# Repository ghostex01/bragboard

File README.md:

# bragboard
 Repository for my first custom (split) keyboard

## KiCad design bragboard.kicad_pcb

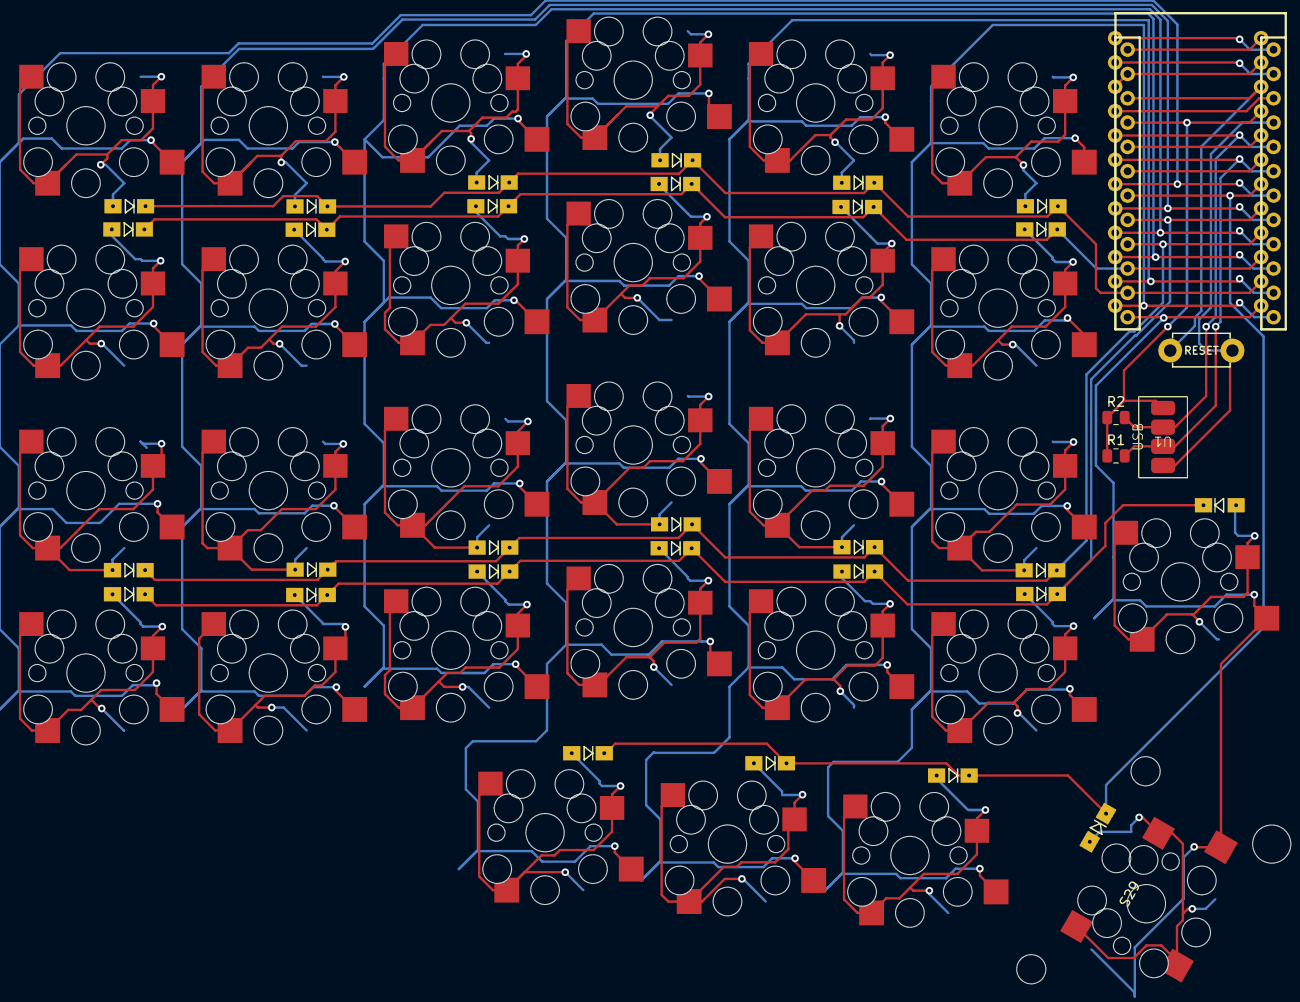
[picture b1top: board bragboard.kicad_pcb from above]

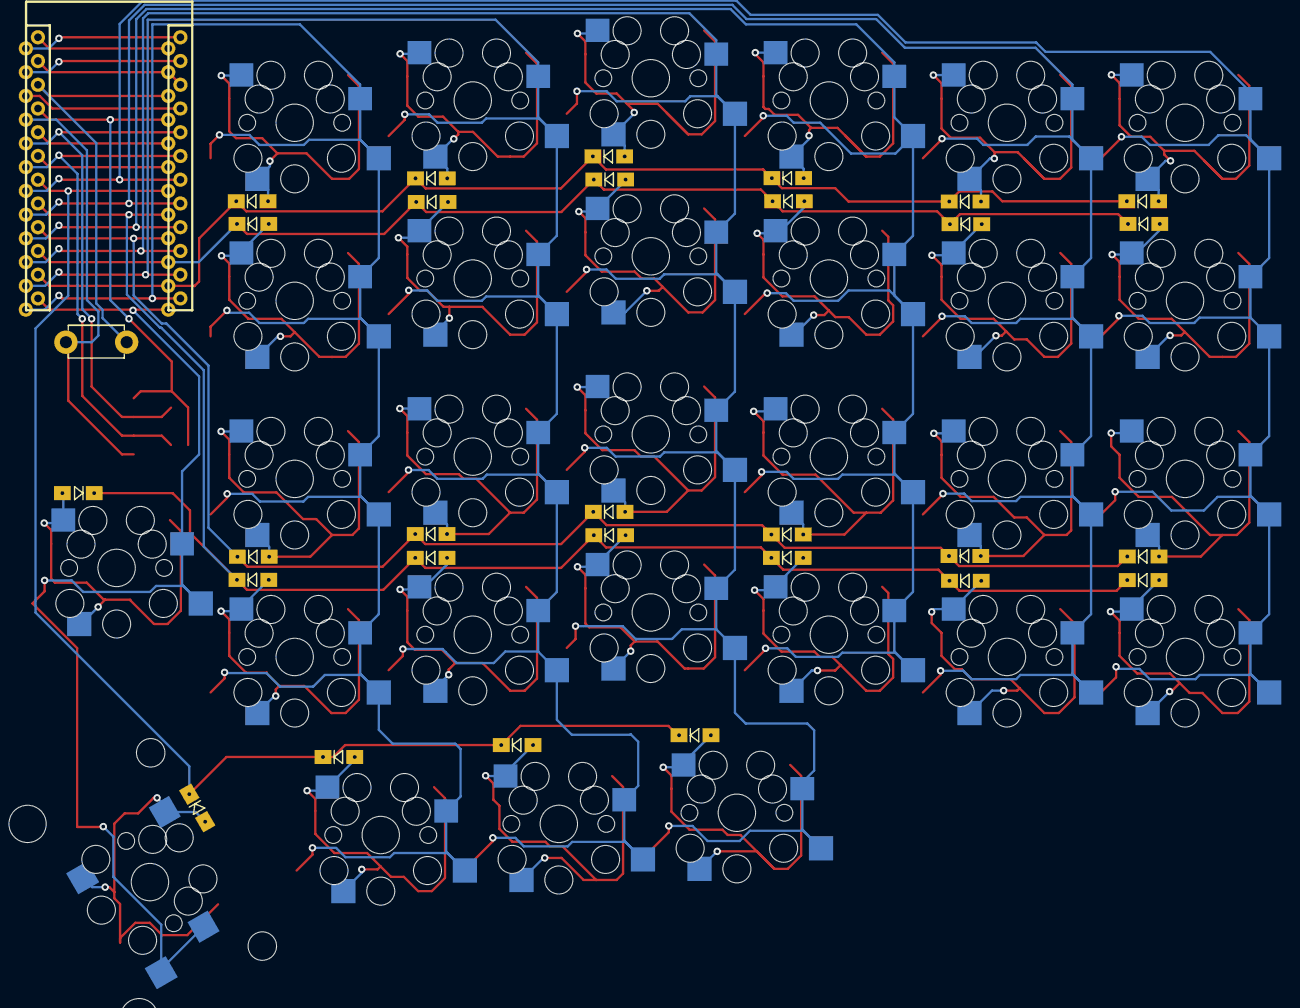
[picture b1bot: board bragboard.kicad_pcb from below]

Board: 2 copper layers, 64 parts (29 on the bottom side), 45 nets.

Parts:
D1, D2, D3, D4, D5, D6, D7, D8, D9, D10, D11, D12, D13, D14, D15, D16, D17, D18, D19, D20, D21, D22, D23, D24, D25, D26, D27, D28, D29: Diode; Diode_SOD123
R1, R2: 4.7K; R_0805_2012Metric
S1, S2, S3, S4, S5, S6, S7, S8, S9, S10, S11, S12, S13, S14, S15, S16, S17, S18, S19, S20, S21, S22, S23, S24, S25, S26, S27, S28, S29: Keyswitch; CherryMX_Hotswap
S29#2: Keyswitch; Stabilizer_MX_2.00u
SW2: SW_Push; RESET2
U1: 4pin_USB_on_PCB
U3: Arduino_Pro_Micro; ProMicro2

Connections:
GND: SW2.2, U1.1 (VCC), U3.3 (GND), U3.4 (GND), U3.23 (GND)
unnamed: D1.2 (A), S1.1, S1.2
unnamed: D2.2 (A), S2.1, S2.2
unnamed: D3.2 (A), S3.1, S3.2
unnamed: D4.2 (A), S4.1, S4.2
unnamed: D5.2 (A), S5.1, S5.2
unnamed: D6.2 (A), S6.1, S6.2
unnamed: D7.2 (A), S7.1, S7.2
unnamed: D8.2 (A), S8.1, S8.2
unnamed: D9.2 (A), S9.1, S9.2
unnamed: D10.2 (A), S10.1, S10.2
unnamed: D11.2 (A), S11.1, S11.2
unnamed: D12.2 (A), S12.1, S12.2
unnamed: D13.2 (A), S13.1, S13.2
unnamed: D14.2 (A), S14.1, S14.2
unnamed: D15.2 (A), S15.1, S15.2
unnamed: D16.2 (A), S16.1, S16.2
unnamed: D17.2 (A), S17.1, S17.2
unnamed: D18.2 (A), S18.1, S18.2
unnamed: D19.2 (A), S19.1, S19.2
unnamed: D20.2 (A), S20.1, S20.2
unnamed: D21.2 (A), S21.1, S21.2
unnamed: D22.2 (A), S22.1, S22.2
unnamed: D23.2 (A), S23.1, S23.2
unnamed: D24.2 (A), S28.1, S28.2
unnamed: D25.2 (A), S25.1, S25.2
unnamed: D26.2 (A), S26.1, S26.2
unnamed: D27.2 (A), S27.1, S27.2
unnamed: D29.2 (A), S29.1, S29.2
unnamed: R1.2, U1.2 (D+), U3.6 (3/PD0)
unnamed: R2.2, U1.3 (D-), U3.5 (2/PD1)
unnamed: SW2.1, U3.22 (RST)
VCC: R1.1, R2.1, U1.4 (GND), U3.21 (VCC)
col0: S1.1, S7.1, S13.1, S19.1, U3.7 (4/PD4)
col1: S2.1, S8.1, S14.1, S20.1, U3.8 (5/PC6)
col2: S3.1, S9.1, S15.1, S21.1, U3.9 (6/PD7)
col3: S4.1, S10.1, S16.1, S22.1, S25.1, U3.10 (7/PE6)
col4: S5.1, S11.1, S17.1, S23.1, S26.1, U3.11 (8/PB4)
col5: S6.1, S12.1, S18.1, S24.1, S27.1, U3.12 (9/PB5)
col6: S28.1, S29.1, U3.13 (10/PB6)
row0: D1.1 (K), D2.1 (K), D3.1 (K), D4.1 (K), D5.1 (K), D6.1 (K), U3.14 (16/PB2)
row1: D7.1 (K), D8.1 (K), D9.1 (K), D10.1 (K), D11.1 (K), D12.1 (K), U3.15 (14/PB3)
row2: D13.1 (K), D14.1 (K), D15.1 (K), D16.1 (K), D17.1 (K), D18.1 (K), U3.16 (15/PB1)
row3: D19.1 (K), D20.1 (K), D21.1 (K), D22.1 (K), D23.1 (K), D24.1 (K), D28.1 (K), U3.17 (A0/PF7)
row4: D25.1 (K), D26.1 (K), D27.1 (K), D29.1 (K), U3.18 (A1/PF6)

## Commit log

2024-02-17 Add submodules
2024-02-18 best library for my keyboard
